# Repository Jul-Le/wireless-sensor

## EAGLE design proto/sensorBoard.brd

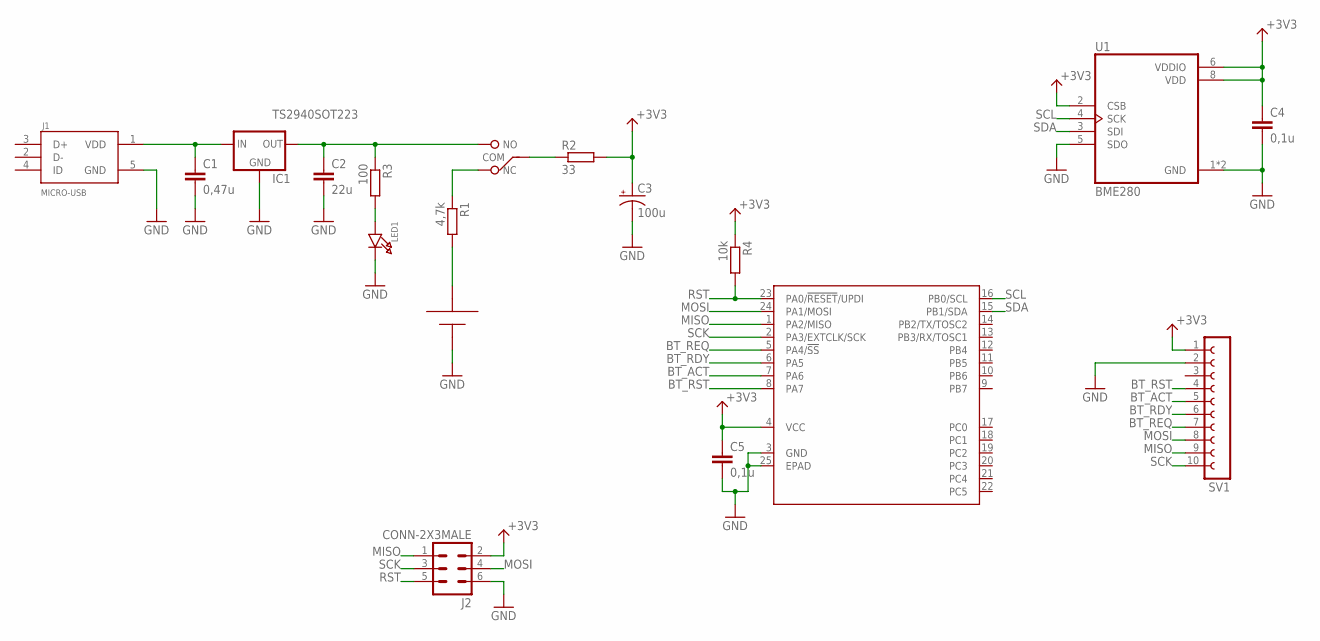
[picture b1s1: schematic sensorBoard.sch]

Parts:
C1: 0,47u; C0805K
C2: 22u; C0805K
C3: 100u; CAPAE660X800
C4, C5: 0,1u; C0805K
IC1: TS2940SOT223; SOT230P700X180-4
J1: MICRO-USB; MOLEX_105017-0001
J2: CONN-2X3MALE; HDRV6W64P254_2X3_762X508X838B
LED1: LED0805
R1: 4,7k; R0805
R2: 33; R0805
R3: 100; R0805
R4: 10k; R0805
SV1: FE10-1; FE10
SW1: SWITCH; EG1215AA
U1: BME280; PSON65P250X250X100-8N
U$1: ATTINY3217TQFN-24; QFN50P400X400X80-25T270
U$3: CR24773039; CR2477

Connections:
+3V3: C3.1 (+), C4.1, C5.1, J2.2, R2.2, R4.1, SV1.1, U1.2 (CSB), U1.6 (VDDIO), U1.8 (VDD), U$1.4 (VCC)
BT_ACT: SV1.5, U$1.7 (PA6)
BT_RDY: SV1.6, U$1.6 (PA5)
BT_REQ: SV1.7, U$1.5 (PA4/!SS!)
BT_RST: SV1.4, U$1.8 (PA7)
GND: C1.2, C2.2, C4.2, C5.2, IC1.2 (GND), IC1.4 (GND), J1.5 (GND), J2.6, LED1.K (C), SV1.2, U1.1 (GND), U1.5 (SDO), U1.7 (GND), U$1.3 (GND), U$1.25 (EPAD), U$3.P$3 (N)
MISO: J2.1, SV1.9, U$1.1 (PA2/MISO)
MOSI: J2.4, SV1.8, U$1.24 (PA1/MOSI)
unnamed: R1.1, SW1.1 (NC)
unnamed: C1.1, IC1.1 (IN), J1.1 (VDD)
unnamed: C2.1, IC1.3 (OUT), R3.1, SW1.3 (NO)
unnamed: R1.2, U$3.P$1, U$3.P$2
unnamed: R2.1, SW1.2 (COM)
unnamed: LED1.A, R3.2
RST: J2.5, R4.2, U$1.23 (PA0/!RESET!/UPDI)
SCK: J2.3, SV1.10, U$1.2 (PA3/EXTCLK/SCK)
SCL: U1.4 (SCK), U$1.16 (PB0/SCL)
SDA: U1.3 (SDI), U$1.15 (PB1/SDA)

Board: 2 copper layers, 18 parts (0 on the bottom side), 18 nets, no tracks yet.

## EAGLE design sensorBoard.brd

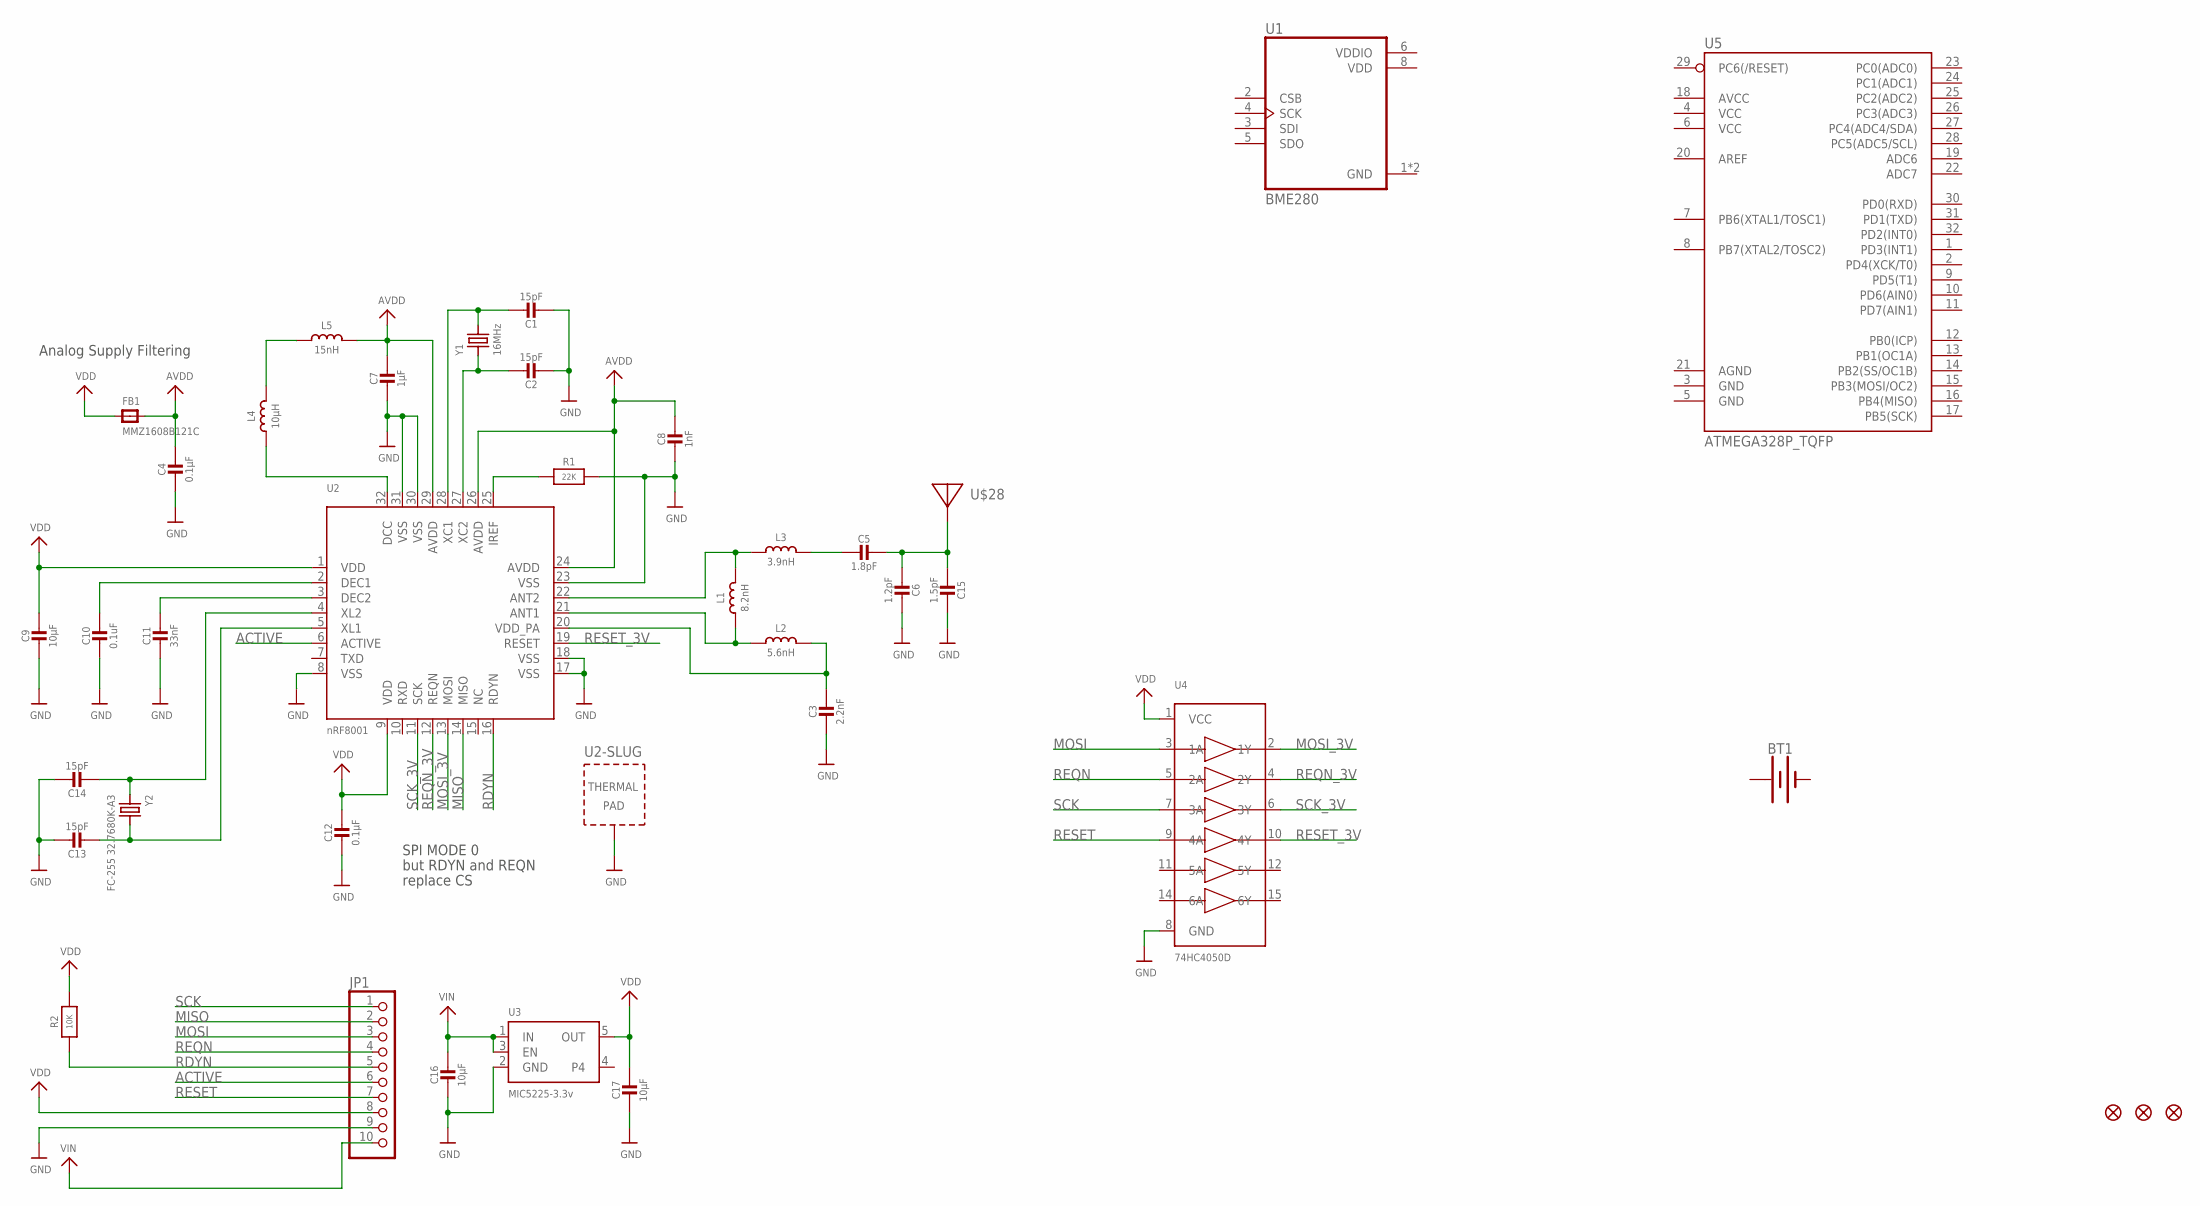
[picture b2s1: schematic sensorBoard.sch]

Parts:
BT1: BATTERY-20MM_PTH; BATTCOM_20MM_PTH
C1, C2, C13, C14: 15pF; 0805-NO
C3: 2.2nF; _0402
C4, C12: 0.1µF; 0805-NO
C5: 1.8pF; _0402MP
C6: 1.2pF; _0402MP
C7: 1µF; 0805-NO
C8: 1nF; _0603
C9, C16, C17: 10µF; 0805-NO
C10: 0.1uF; 0805-NO
C11: 33nF; 0805-NO
C15: 1.5pF; _0402MP
FB1: MMZ1608B121C; 0805
FID1, FID2, FID3: FIDUCIAL""; FIDUCIAL_1MM
JP1: HEADER-1X1070MIL; 1X10_ROUND70
L1: 8.2nH; _0402
L2: 5.6nH; _0402
L3: 3.9nH; _0402
L4: 10µH; _0603
L5: 15nH; _0603
R1: 22K; _0805MP
R2: 10K; 0805-NO
U1: BME280; PSON65P250X250X100-8N
U2: nRF8001; QFN32_5MM
U3: MIC5225-3.3v; SOT23-5
U4: 74HC4050D; TSSOP16
U5: ATMEGA328P_TQFP; TQFP32-08
U$28: ANTENNA_PCBNRF8001_1.6MM; ANT_PCB_2.4GHZ_NRF8001_1.6MM_1OZ
Y1: 16MHz; CRYSTAL_3.2X2.5
Y2: FC-255 32.7680K-A3; CRYSTAL_8X3.8

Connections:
+: BT1.1 (+)
+3.3V: C9.1, C12.1, C17.1, FB1.1, JP1.8, R2.2, U1.8 (VDD), U2.1 (VDD), U2.9 (VDD), U3.5 (OUT), U4.1 (VCC)
-: BT1.2 (-)
ACTIVE: JP1.6, U2.6 (ACTIVE)
AVDD: C4.1, C7.1, C8.1, FB1.2, L5.2, U2.24 (AVDD), U2.26 (AVDD), U2.29 (AVDD)
GND: C1.2, C2.2, C3.2, C4.2, C6.1, C7.2, C8.2, C9.2, C10.2, C11.2, C12.2, C13.1, C14.1, C15.1, C16.2, C17.2, JP1.9, R1.2, U1.1 (GND), U1.7 (GND), U2.8 (VSS), U2.17 (VSS), U2.18 (VSS), U2.23 (VSS), U2.30 (VSS), U2.31 (VSS), U2.33 (TP), U3.2 (GND), U4.8 (GND)
MISO: JP1.2, U2.14 (MISO)
MOSI: JP1.3, U4.3 (1A)
MOSI_3V: U2.13 (MOSI), U4.2 (1Y)
unnamed: L1.2, L3.1, U2.22 (ANT2)
unnamed: L1.1, L2.1, U2.21 (ANT1)
unnamed: C3.1, L2.2, U2.20 (VDD_PA)
unnamed: L4.2, L5.1
unnamed: C5.2, L3.2
unnamed: C11.1, U2.3 (DEC2)
unnamed: C10.1, U2.2 (DEC1)
unnamed: C1.1, U2.28 (XC1), Y1.2
unnamed: C2.1, U2.27 (XC2), Y1.1
unnamed: L4.1, U2.32 (DCC)
unnamed: R1.1, U2.25 (IREF)
unnamed: C5.1, C6.2, C15.2, U$28.FEED
unnamed: C14.2, U2.4 (XL2), Y2.P$1 (1)
unnamed: C13.2, U2.5 (XL1), Y2.P$4 (2)
RDYN: JP1.5, R2.1, U2.16 (RDYN)
REQN: JP1.4, U4.5 (2A)
REQN_3V: U2.12 (REQN), U4.4 (2Y)
RESET: JP1.7, U4.9 (4A)
RESET_3V: U2.19 (RESET), U4.10 (4Y)
SCK: JP1.1, U4.7 (3A)
SCK_3V: U2.11 (SCK), U4.6 (3Y)
VDDIO: U1.6 (VDDIO)
VIN: C16.1, JP1.10, U3.1 (IN), U3.3 (EN)

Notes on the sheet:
Analog Supply Filtering
SPI MODE 0
but RDYN and REQN
replace CS

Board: 2 copper layers, 38 parts (0 on the bottom side), 29 nets, no tracks yet.

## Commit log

2019-07-08 Created proto PCB

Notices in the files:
parts and their libraries:
microbuilder: This work is placed in the public domain, and may be freely used for commercial and non-commercial work with the following conditions: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
SparkFun-IC-Microcontroller: Licensing: Creative Commons ShareAlike 4.0 International - https://creativecommons.org/licenses/by-sa/4.0
